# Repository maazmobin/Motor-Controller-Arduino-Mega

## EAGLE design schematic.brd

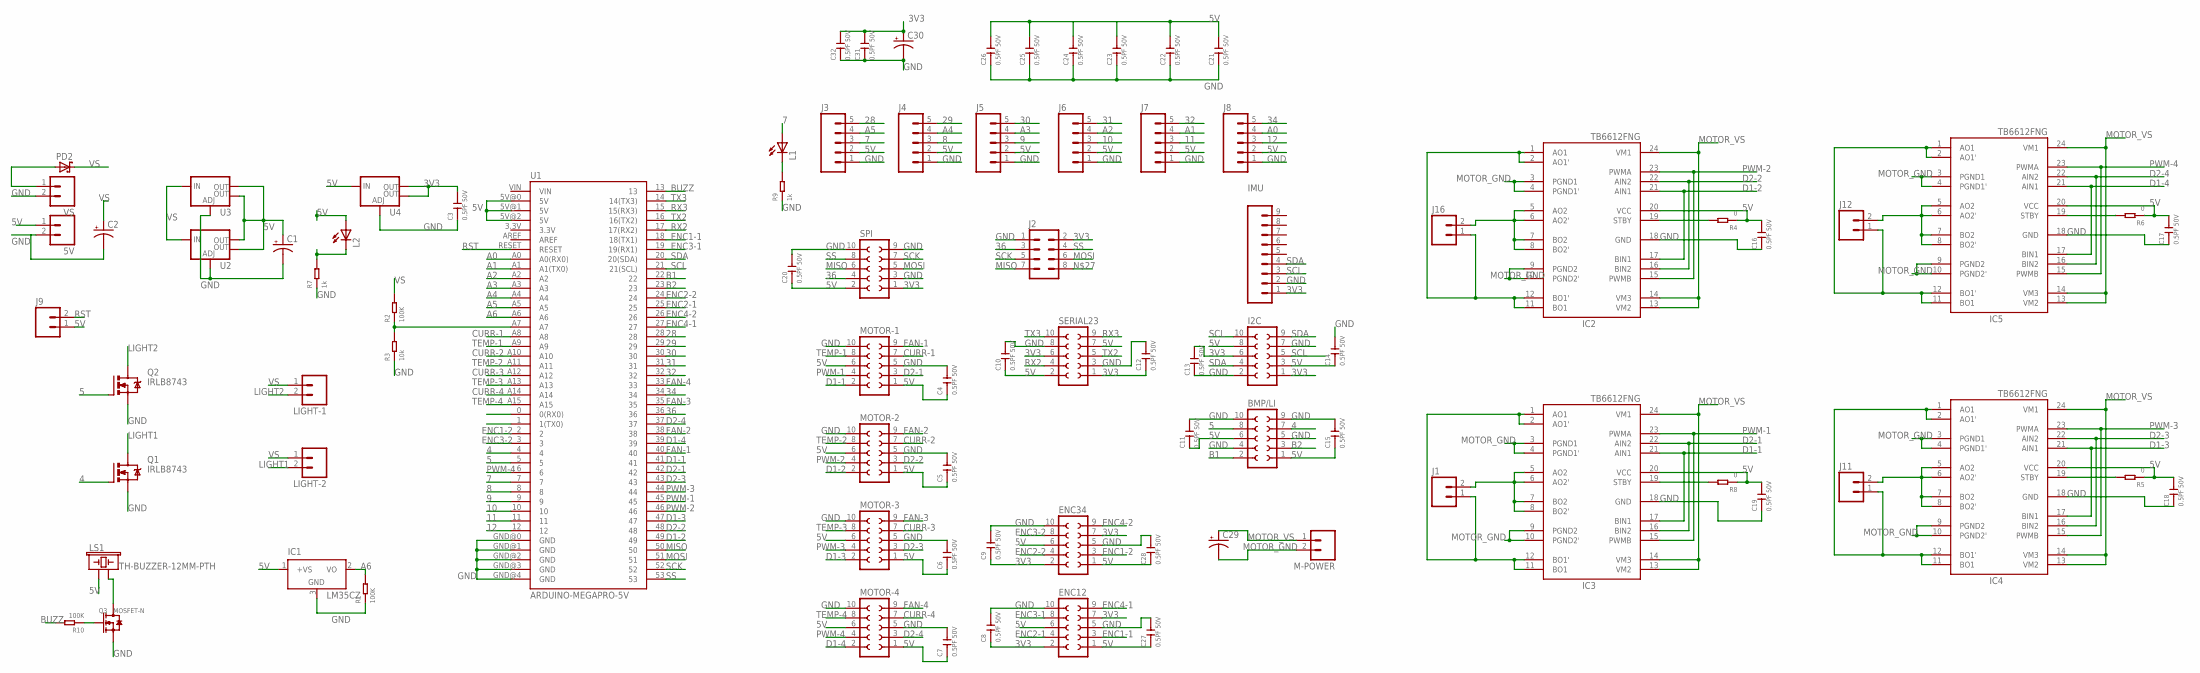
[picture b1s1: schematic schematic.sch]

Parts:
5V: M025MM; SCREWTERMINAL-5MM-2
BMP/LI: SOCKET-10V; S10V
C1, C2, C29, C30: CAP_POLPTH1; CPOL-RADIAL-100UF-25V
C3, C4, C5, C6, C7, C8, C9, C10, C11, C12, C13, C14, C15, C16, C17, C18, C19, C20, C21, C22, C23, C24, C25, C26, C27, C28, C31, C32: 0.5PF 50V; C0603
ENC12, ENC34: SOCKET-10V; S10V
I2C: SOCKET-10V; S10V
IC1: LM35CZ; TO92
IC2, IC3, IC4, IC5: TB6612FNG; SSOP24
IMU: M09; 1X09
J1, J11, J12, J16: M025MM; SCREWTERMINAL-5MM-2
J2: M04X2; 2X4
J3, J4, J5, J6, J7, J8: M05PTH; 1X05
J9: M02PTH; 1X02
L1, L2: LEDCHIP-LED0603; CHIP-LED0603
LIGHT-1, LIGHT-2: M025MM; SCREWTERMINAL-5MM-2
LS1: TH-BUZZER-12MM-PTH; BUZZER-12MM
M-POWER: M025MM; SCREWTERMINAL-5MM-2
MOTOR-1, MOTOR-2, MOTOR-3, MOTOR-4: SOCKET-10V; S10V
PD2: SCHOTTKY-DIODEF126Z12; F126Z12
Q1, Q2: IRLB8743; TO220BV
Q3: MOSFET-N; SOT-23
R1, R2, R10: 100K; R0603
R3: 10k; R0603
R4, R5, R6, R8: 0; R0603
R7, R9: 1k; R0603
SERIAL23: SOCKET-10V; S10V
SPI: SOCKET-10V; S10V
U1: ARDUINO-MEGAPRO-5V; ARDUINO_MEGA-PRO-5V
U2, U3, U4: V_REG_LM1117SOT223; SOT223
VS: M025MM; SCREWTERMINAL-5MM-2

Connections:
3V3: C3.2, C8.1, C9.1, C12.1, C13.2, C30.1 (+), C31.2, C32.2, ENC12.2, ENC12.7, ENC34.2, ENC34.7, I2C.1, I2C.6, IMU.1, J2.2, SERIAL23.1, SERIAL23.6, SPI.1, U4.2 (OUT), U4.4 (OUT)
4: BMP/LI.7, Q1.G, U1.4
5: BMP/LI.8, Q2.G, U1.5
5V: 5V.1, BMP/LI.1, BMP/LI.6, C1.1 (+), C4.1, C5.1, C6.1, C7.1, C10.1, C11.1, C14.1, C15.1, C16.2, C17.2, C18.2, C19.2, C20.1, C21.2, C22.2, C23.2, C24.2, C25.2, C26.2, C27.1, C28.1, ENC12.1, ENC12.6, ENC34.1, ENC34.6, I2C.3, I2C.8, IC1.1 (+VS), IC2.20 (VCC), IC3.20 (VCC), IC4.20 (VCC), IC5.20 (VCC), J3.2, J4.2, J5.2, J6.2, J7.2, J8.2, J9.1, L2.A, LS1.+ (1), MOTOR-1.1, MOTOR-1.6, MOTOR-2.1, MOTOR-2.6, MOTOR-3.1, MOTOR-3.6, MOTOR-4.1, MOTOR-4.6, R4.1, R5.1, R6.1, R8.1, SERIAL23.2, SERIAL23.7, SPI.2, U1.5V@0 (5V), U1.5V@1 (5V), U1.5V@2 (5V), U2.2 (OUT), U2.4 (OUT), U3.2 (OUT), U3.4 (OUT), U4.3 (IN)
7: J3.3, L1.A, U1.7
8: J4.3, U1.8
9: J5.3, U1.9
10: J6.3, U1.10
11: J7.3, U1.11
12: J8.3, U1.12
28: J3.5, U1.28
29: J4.5, U1.29
30: J5.5, U1.30
31: J6.5, U1.31
32: J7.5, U1.32
34: J8.5, U1.34
36: J2.3, SPI.4, U1.36
A0: J8.4, U1.A0 (A0(RX0))
A1: J7.4, U1.A1 (A1(TX0))
A2: J6.4, U1.A2
A3: J5.4, U1.A3
A4: J4.4, U1.A4
A5: J3.4, U1.A5
A6: IC1.2 (VO), R1.2, U1.A6
B1: BMP/LI.2, U1.22
B2: BMP/LI.3, U1.23
BUZZ: R10.2, U1.13
CURR-1: MOTOR-1.7, U1.A8
CURR-2: MOTOR-2.7, U1.A10
CURR-3: MOTOR-3.7, U1.A12
CURR-4: MOTOR-4.7, U1.A14
D1-1: IC3.17 (BIN1), IC3.21 (AIN1), MOTOR-1.2, U1.41
D1-2: IC2.17 (BIN1), IC2.21 (AIN1), MOTOR-2.2, U1.49
D1-3: IC4.17 (BIN1), IC4.21 (AIN1), MOTOR-3.2, U1.47
D1-4: IC5.17 (BIN1), IC5.21 (AIN1), MOTOR-4.2, U1.39
D2-1: IC3.16 (BIN2), IC3.22 (AIN2), MOTOR-1.3, U1.42
D2-2: IC2.16 (BIN2), IC2.22 (AIN2), MOTOR-2.3, U1.48
D2-3: IC4.16 (BIN2), IC4.22 (AIN2), MOTOR-3.3, U1.43
D2-4: IC5.16 (BIN2), IC5.22 (AIN2), MOTOR-4.3, U1.37
ENC1-1: ENC12.3, U1.18 (18(TX1))
ENC1-2: ENC34.3, U1.2
ENC2-1: ENC12.4, U1.25
ENC2-2: ENC34.4, U1.24
ENC3-1: ENC12.8, U1.19 (19(RX1))
ENC3-2: ENC34.8, U1.3
ENC4-1: ENC12.9, U1.27
ENC4-2: ENC34.9, U1.26
FAN-1: MOTOR-1.9, U1.40
FAN-2: MOTOR-2.9, U1.38
FAN-3: MOTOR-3.9, U1.35
FAN-4: MOTOR-4.9, U1.33
GND: 5V.2, BMP/LI.4, BMP/LI.5, BMP/LI.9, BMP/LI.10, C1.2 (-), C2.2 (-), C3.1, C4.2, C5.2, C6.2, C7.2, C8.2, C9.2, C10.2, C11.2, C12.2, C13.1, C14.2, C15.2, C16.1, C17.1, C18.1, C19.1, C20.2, C21.1, C22.1, C23.1, C24.1, C25.1, C26.1, C27.2, C28.2, C30.2 (-), C31.1, C32.1, ENC12.5, ENC12.10, ENC34.5, ENC34.10, I2C.2, I2C.7, IC1.3 (GND), IC2.18 (GND), IC3.18 (GND), IC4.18 (GND), IC5.18 (GND), IMU.2, J2.1, J3.1, J4.1, J5.1, J6.1, J7.1, J8.1, MOTOR-1.5, MOTOR-1.10, MOTOR-2.5, MOTOR-2.10, MOTOR-3.5, MOTOR-3.10, MOTOR-4.5, MOTOR-4.10, Q1.S, Q2.S, Q3.2 (S), R1.1, R3.1, R7.1, R9.1, SERIAL23.3, SERIAL23.8, SPI.3, SPI.9, SPI.10, U1.GND@0 (GND), U1.GND@1 (GND), U1.GND@2 (GND), U1.GND@3 (GND), U1.GND@4 (GND), U2.1 (ADJ), U3.1 (ADJ), U4.1 (ADJ), VS.2
LIGHT1: LIGHT-2.2, Q1.D
LIGHT2: LIGHT-1.2, Q2.D
MISO: J2.7, SPI.6, U1.50
MOSI: J2.6, SPI.5, U1.51
MOTOR_GND: C29.2 (-), IC2.3 (PGND1), IC2.4 (PGND1'), IC2.9 (PGND2), IC2.10 (PGND2'), IC3.3 (PGND1), IC3.4 (PGND1'), IC3.9 (PGND2), IC3.10 (PGND2'), IC4.3 (PGND1), IC4.4 (PGND1'), IC4.9 (PGND2), IC4.10 (PGND2'), IC5.3 (PGND1), IC5.4 (PGND1'), IC5.9 (PGND2), IC5.10 (PGND2'), M-POWER.2
MOTOR_VS: C29.1 (+), IC2.13 (VM2), IC2.14 (VM3), IC2.24 (VM1), IC3.13 (VM2), IC3.14 (VM3), IC3.24 (VM1), IC4.13 (VM2), IC4.14 (VM3), IC4.24 (VM1), IC5.13 (VM2), IC5.14 (VM3), IC5.24 (VM1), M-POWER.1
unnamed: PD2.A, VS.1
unnamed: IC3.5 (AO2), IC3.6 (AO2'), IC3.7 (BO2), IC3.8 (BO2'), J1.2
unnamed: IC2.5 (AO2), IC2.6 (AO2'), IC2.7 (BO2), IC2.8 (BO2'), J16.2
unnamed: IC3.1 (AO1), IC3.2 (AO1'), IC3.11 (BO1), IC3.12 (BO1'), J1.1
unnamed: IC2.1 (AO1), IC2.2 (AO1'), IC2.11 (BO1), IC2.12 (BO1'), J16.1
unnamed: LS1.- (2), Q3.3 (D)
unnamed: Q3.1 (G), R10.1
unnamed: R2.1, R3.2, U1.A7
unnamed: IC3.19 (STBY), R8.2
unnamed: IC2.19 (STBY), R4.2
unnamed: IC4.5 (AO2), IC4.6 (AO2'), IC4.7 (BO2), IC4.8 (BO2'), J11.2
unnamed: IC4.1 (AO1), IC4.2 (AO1'), IC4.11 (BO1), IC4.12 (BO1'), J11.1
unnamed: L1.C, R9.2
unnamed: IC4.19 (STBY), R5.2
unnamed: IC5.5 (AO2), IC5.6 (AO2'), IC5.7 (BO2), IC5.8 (BO2'), J12.2
unnamed: IC5.1 (AO1), IC5.2 (AO1'), IC5.11 (BO1), IC5.12 (BO1'), J12.1
unnamed: IC5.19 (STBY), R6.2
unnamed: L2.C, R7.2
PWM-1: IC3.15 (PWMB), IC3.23 (PWMA), MOTOR-1.4, U1.45
PWM-2: IC2.15 (PWMB), IC2.23 (PWMA), MOTOR-2.4, U1.46
PWM-3: IC4.15 (PWMB), IC4.23 (PWMA), MOTOR-3.4, U1.44
PWM-4: IC5.15 (PWMB), IC5.23 (PWMA), MOTOR-4.4, U1.6
RST: J9.2, U1.RESET
RX2: SERIAL23.4, U1.17 (17(RX2))
RX3: SERIAL23.9, U1.15 (15(RX3))
SCK: J2.5, SPI.7, U1.52
SCL: I2C.5, I2C.10, IMU.3, U1.21 (21(SCL))
SDA: I2C.4, I2C.9, IMU.4, U1.20 (20(SDA))
SS: J2.4, SPI.8, U1.53
TEMP-1: MOTOR-1.8, U1.A9
TEMP-2: MOTOR-2.8, U1.A11
TEMP-3: MOTOR-3.8, U1.A13
TEMP-4: MOTOR-4.8, U1.A15
TX2: SERIAL23.5, U1.16 (16(TX2))
TX3: SERIAL23.10, U1.14 (14(TX3))
VS: C2.1 (+), LIGHT-1.1, LIGHT-2.1, PD2.C, R2.2, U2.3 (IN), U3.3 (IN)

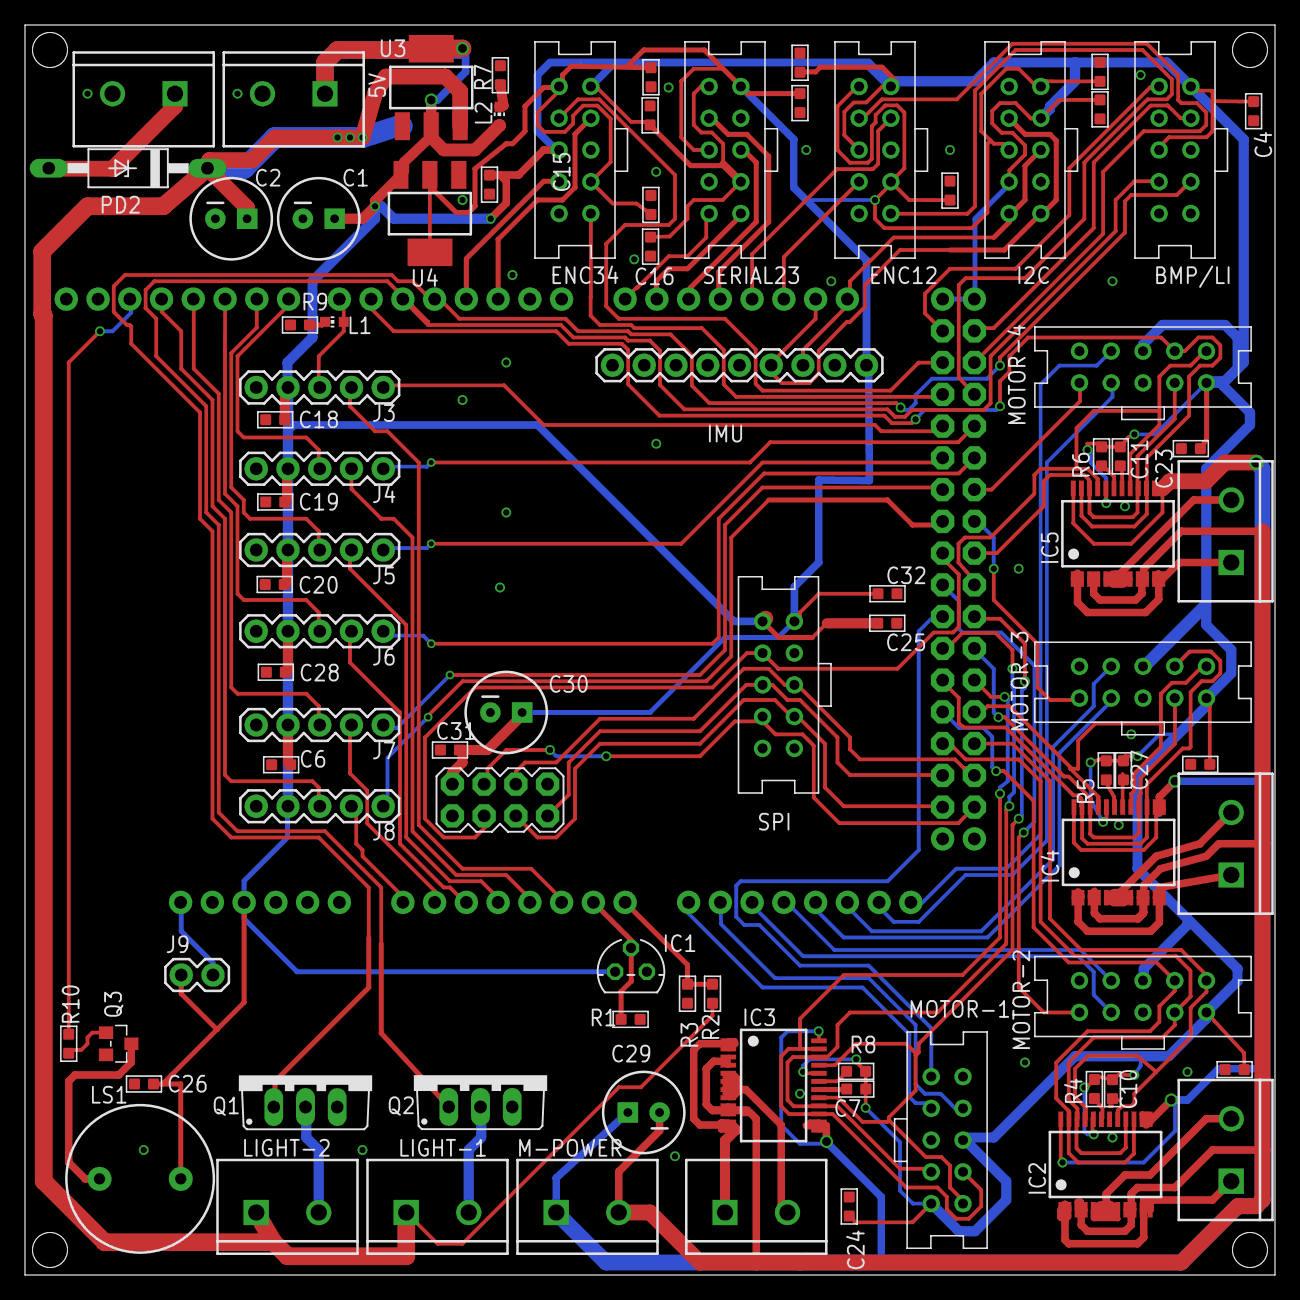
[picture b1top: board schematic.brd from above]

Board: 2 copper layers, 100.0 x 100.0 mm, 86 parts (1 on the bottom side), 94 nets.

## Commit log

2017-07-21 :tada: Added .gitattributes & .gitignore files
2017-07-21 basic schematic completed
2017-07-21 schematic completed , final review required
2017-07-24 update 1: idc connector
2017-07-26 on layout
2017-07-26 on layout 2
2017-07-28 layout adjustment
2017-08-01 layout complete
2017-08-01 SILK COMPLETE
2017-08-04 completed

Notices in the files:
parts and their libraries:
SparkFun-Boards: Licensing: Creative Commons ShareAlike 4.0 International - https://creativecommons.org/licenses/by-sa/4.0
